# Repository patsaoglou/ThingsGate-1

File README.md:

#   ThingsGate-1

Gateway Motherboard powered by the ThingsCore-1 SOM. Featuring a LTE Modem, a LoraWAN Concentrator, PoE, battery power and solar charging, it is capable of supporting off-grid IoT applications.

#   Realistic View (Comming Soon...)

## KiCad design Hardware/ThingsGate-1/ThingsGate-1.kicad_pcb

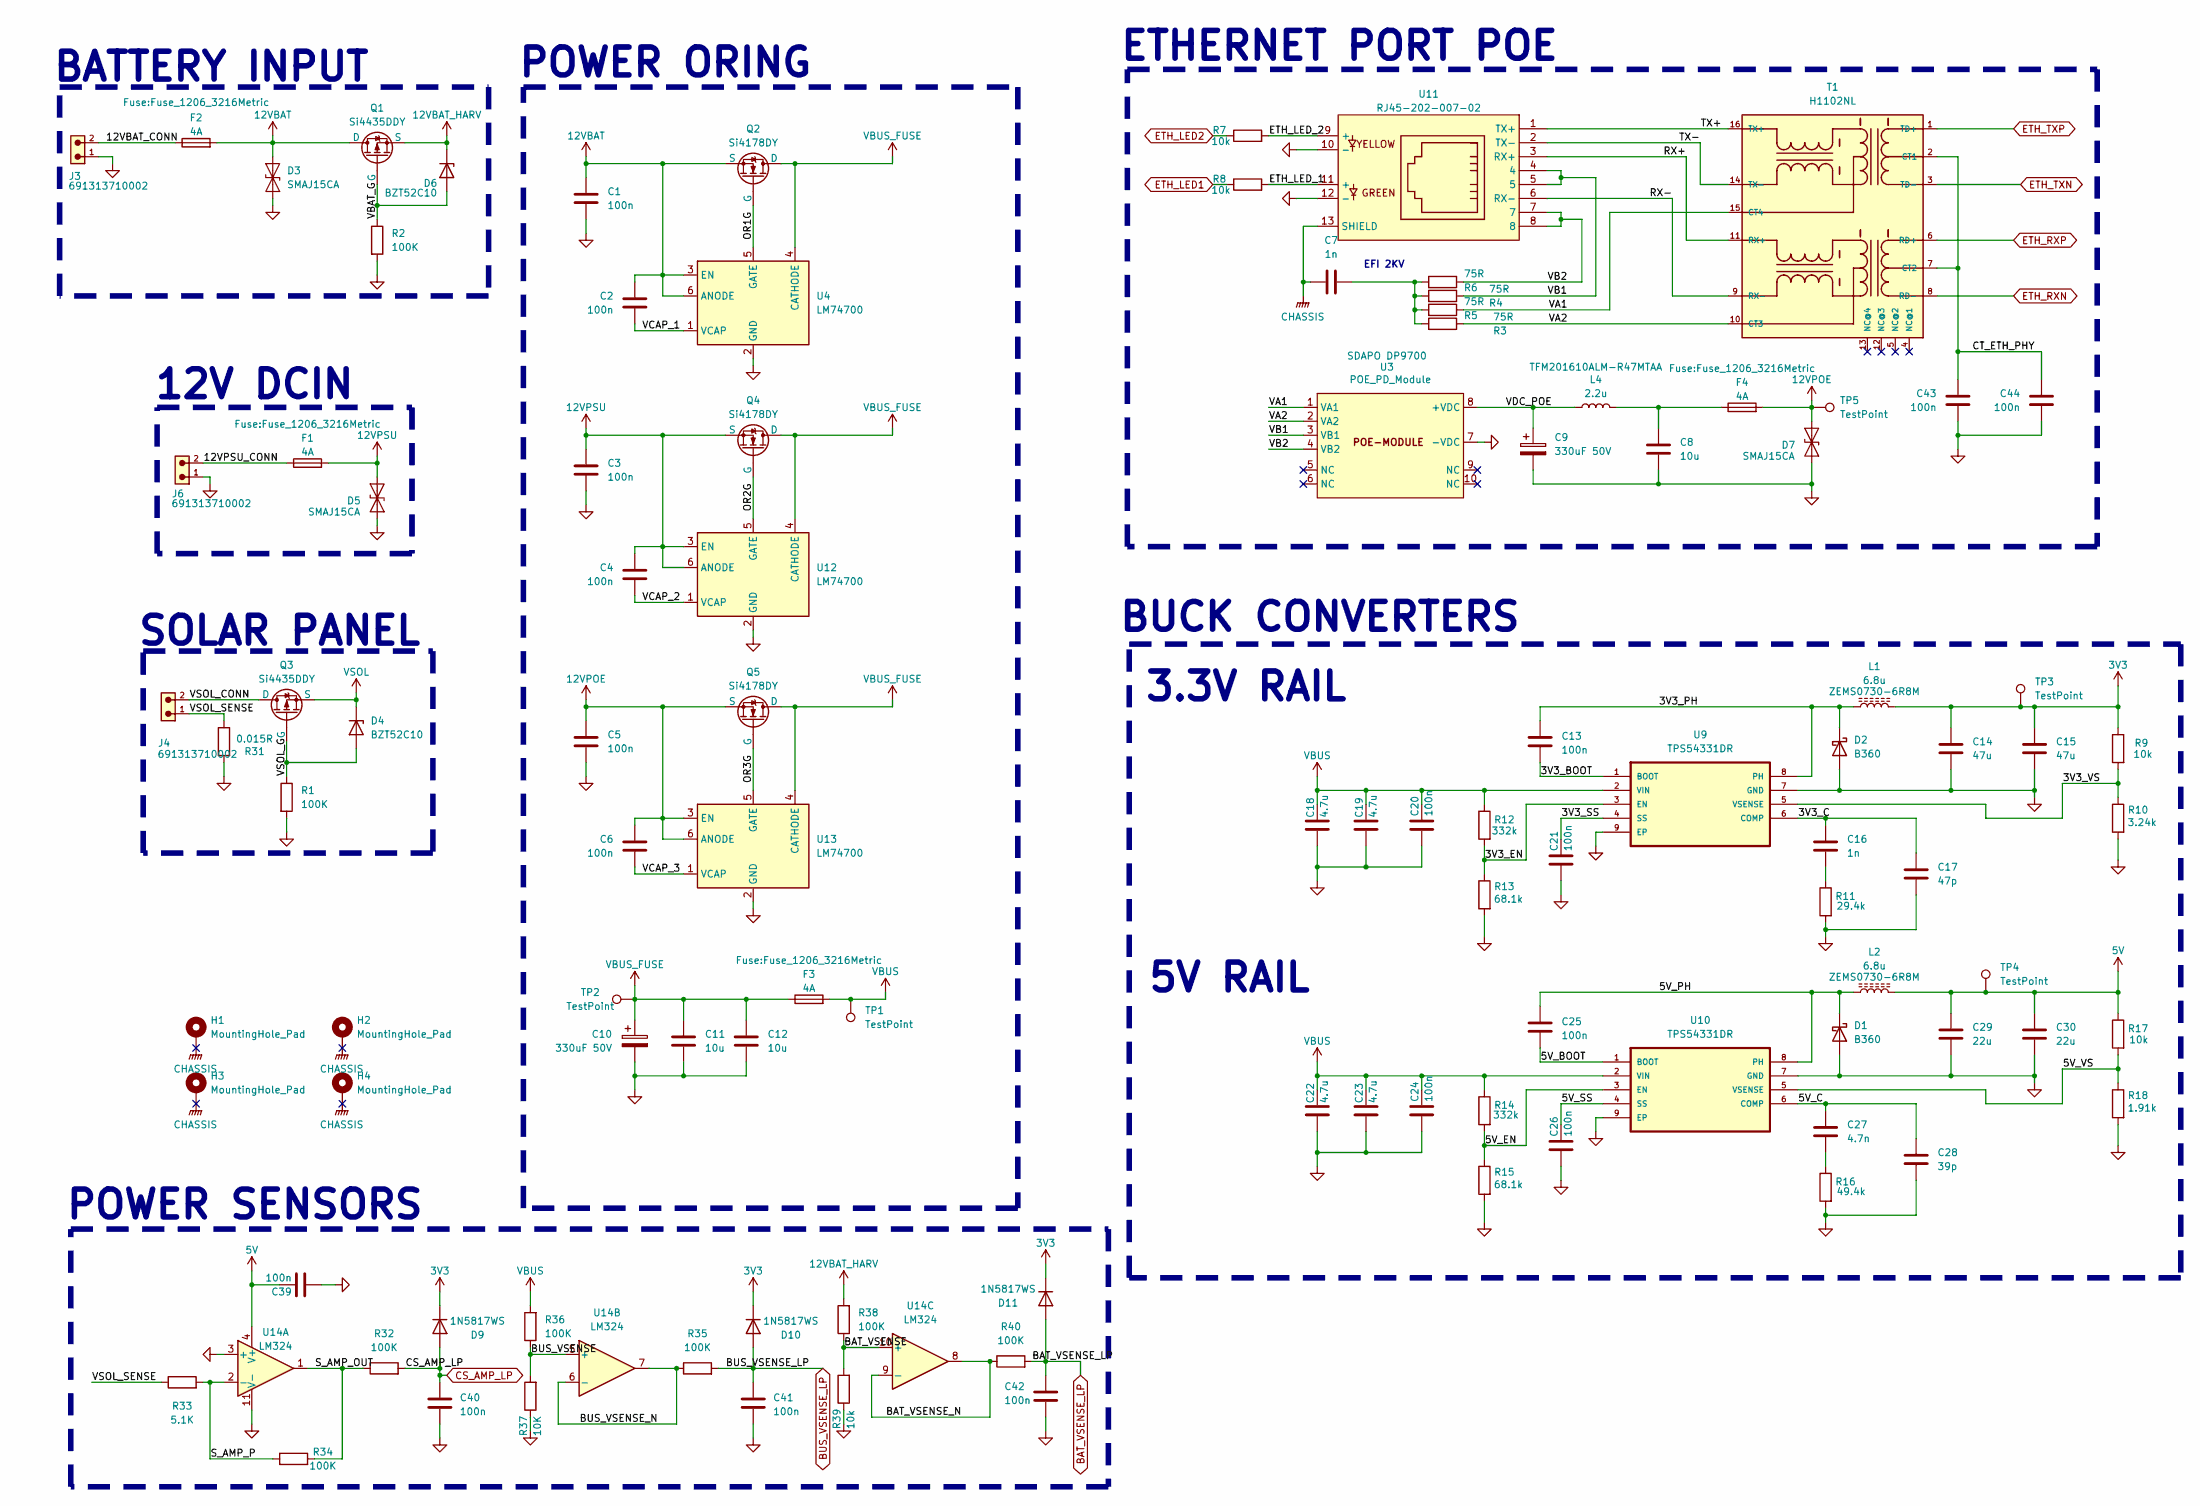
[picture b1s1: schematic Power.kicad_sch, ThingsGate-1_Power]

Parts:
C1, C2, C3, C4, C5, C6, C13, C20, C21, C24, C25, C26, C39, C40, C41, C42, C43, C44: 100n; C_0603_1608Metric
C7: 1n; C_1206_3216Metric
C8: 10u; Fuse_0805_2012Metric
C9, C10: 330uF 50V; CP_Elec_10x10.5
C11, C12: 10u; C_0805_2012Metric
C14, C15: 47u; C_0805_2012Metric
C16: 1n; C_0603_1608Metric
C17: 47p; C_0603_1608Metric
C18, C19, C22, C23: 4.7u; C_0805_2012Metric
C27: 4.7n; C_0603_1608Metric
C28: 39p; C_0603_1608Metric
C29, C30: 22u; C_0805_2012Metric
D1, D2: B360; D_SMA
D3, D5, D7: SMAJ15CA; D_SMA
D4, D6: BZT52C10; D_SOD-123
D9, D10, D11: 1N5817WS; D_SOD-323
F1, F2, F3, F4: 4A; Fuse_1206_3216Metric
H1, H2, H3, H4: MountingHole_Pad; MountingHole_3.2mm_M3_DIN965_Pad_TopBottom
J3, J4, J6: 691313710002
L1, L2: 6.8u; L_0730-6R8M
L4: 2.2u; L_0805_2016
Q1, Q3: Si4435DDY; SO-8_3.9x4.9mm_P1.27mm
Q2, Q4, Q5: Si4178DY; SO-8_3.9x4.9mm_P1.27mm
R1, R2, R32, R34, R35, R36, R38, R40: 100K; R_0603_1608Metric
R3, R4, R5, R6: 75R; R_0603_1608Metric
R7, R8, R9, R17, R39: 10k; R_0603_1608Metric
R10: 3.24k; R_0603_1608Metric
R11: 29.4k; R_0603_1608Metric
R12, R14: 332k; R_0603_1608Metric
R13, R15: 68.1k; R_0603_1608Metric
R16: 49.4k; R_0603_1608Metric
R18: 1.91k; R_0603_1608Metric
R31: 0.015R; R_1206_3216Metric
R33: 5.1K; R_0603_1608Metric
R37: 10K; R_0603_1608Metric
T1: H1102NL
TP1, TP2, TP3, TP4, TP5: TestPoint; TestPoint_Pad_D1.5mm
U3: POE_PD_Module; SDAPO_DP9700; Part SDAPO DP9700
U4, U12, U13: LM74700; SOT-23-6
U9, U10: TPS54331DR; TPS54331DDAR_PowerPAD
U11: RJ45-202-007-02; RJ45-TH_RJ45-202-007-02
U14: LM324; SOIC-14_3.9x8.7mm_P1.27mm

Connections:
3V3: C14.1, C15.1, D9.1 (K), D10.1 (K), D11.1 (K), L1.2, R9.1, TP3.1; also elsewhere on the board
5V: C29.1, C30.1, C39.1, L2.2, R17.1, TP4.1, U14.4 (V+); also elsewhere on the board
12VBAT: C1.1, C2.1, D3.2 (A2), F2.2, Q1.5 (D), Q1.6 (D), Q1.7 (D), Q1.8 (D), Q2.1 (S), Q2.2 (S), Q2.3 (S), U4.3 (EN), U4.6 (ANODE)
12VBAT_HARV: D6.1 (K), Q1.1 (S), Q1.2 (S), Q1.3 (S), R38.2; also elsewhere on the board
12VPOE: C5.1, C6.1, D7.2 (A2), F4.2, Q5.1 (S), Q5.2 (S), Q5.3 (S), TP5.1, U13.3 (EN), U13.6 (ANODE)
12VPSU: C3.1, C4.1, D5.2 (A2), F1.2, Q4.1 (S), Q4.2 (S), Q4.3 (S), U12.3 (EN), U12.6 (ANODE)
/Power Supply/3V3_BOOT: C13.2, U9.1 (BOOT)
/Power Supply/3V3_C: C16.1, C17.1, U9.6 (COMP)
/Power Supply/3V3_EN: R12.2, R13.1, U9.3 (EN)
/Power Supply/3V3_PH: C13.1, D2.1 (K), L1.1, U9.8 (PH)
/Power Supply/3V3_SS: C21.1, U9.4 (SS)
/Power Supply/3V3_VS: R9.2, R10.1, U9.5 (VSENSE)
/Power Supply/5V_BOOT: C25.2, U10.1 (BOOT)
/Power Supply/5V_C: C27.1, C28.1, U10.6 (COMP)
/Power Supply/5V_EN: R14.2, R15.1, U10.3 (EN)
/Power Supply/5V_PH: C25.1, D1.1 (K), L2.1, U10.8 (PH)
/Power Supply/5V_SS: C26.1, U10.4 (SS)
/Power Supply/5V_VS: R17.2, R18.1, U10.5 (VSENSE)
/Power Supply/12VBAT_CONN: F2.1, J3.2
/Power Supply/12VPSU_CONN: F1.1, J6.2
/Power Supply/BAT_VSENSE: R38.1, R39.2, U14.10 (+)
/Power Supply/BAT_VSENSE_N: R40.1, U14.8, U14.9 (-)
/Power Supply/BUS_VSENSE: R36.1, R37.2, U14.5 (+)
/Power Supply/BUS_VSENSE_N: R35.1, U14.6 (-), U14.7
/Power Supply/CT_ETH_PHY: C43.1, C44.1, T1.2 (CT1), T1.7 (CT2)
/Power Supply/ETH_LED_1: R8.2, U11.11 (+)
/Power Supply/ETH_LED_2: R7.2, U11.9 (+)
/Power Supply/OR1G: Q2.4 (G), U4.5 (GATE)
/Power Supply/OR2G: Q4.4 (G), U12.5 (GATE)
/Power Supply/OR3G: Q5.4 (G), U13.5 (GATE)
/Power Supply/RX+: T1.11 (RX+), U11.3 (RX+)
/Power Supply/RX-: T1.9 (RX-), U11.6 (RX-)
/Power Supply/S_AMP_OUT: R32.1, R34.2, U14.1
/Power Supply/S_AMP_P: R33.2, R34.1, U14.2 (-)
/Power Supply/TX+: T1.16 (TX+), U11.1 (TX+)
/Power Supply/TX-: T1.14 (TX-), U11.2 (TX-)
/Power Supply/VA1: R5.1, T1.15 (CT4), U3.1 (VA1)
/Power Supply/VA2: R3.1, T1.10 (CT3), U3.2 (VA2)
/Power Supply/VB1: R4.1, U3.3 (VB1), U11.4, U11.5
/Power Supply/VB2: R6.1, U3.4 (VB2), U11.7, U11.8
/Power Supply/VBAT_G: D6.2 (A), Q1.4 (G), R2.1
/Power Supply/VCAP_1: C2.2, U4.1 (VCAP)
/Power Supply/VCAP_2: C4.2, U12.1 (VCAP)
/Power Supply/VCAP_3: C6.2, U13.1 (VCAP)
/Power Supply/VDC_POE: C9.1, L4.1, U3.8 (+VDC)
/Power Supply/VSOL_CONN: J4.2, Q3.5 (D), Q3.6 (D), Q3.7 (D), Q3.8 (D)
/Power Supply/VSOL_G: D4.2 (A), Q3.4 (G), R1.1
/Power Supply/VSOL_SENSE: J4.1, R31.1, R33.1
BAT_VSENSE_LP: C42.2, D11.2 (A), R40.2; also elsewhere on the board
BUS_VSENSE_LP: C41.2, D10.2 (A), R35.2; also elsewhere on the board
CHASSIS: C7.1, H1.1, H2.1, H3.1, H4.1, U11.13 (SHIELD); also elsewhere on the board
CS_AMP_LP: C40.2, D9.2 (A), R32.2; also elsewhere on the board
ETH_LED1: R8.1; also elsewhere on the board
ETH_LED2: R7.1; also elsewhere on the board
ETH_RXN: T1.8 (RD-); also elsewhere on the board
ETH_RXP: T1.6 (RD+); also elsewhere on the board
ETH_TXN: T1.3 (TD-); also elsewhere on the board
ETH_TXP: T1.1 (TD+); also elsewhere on the board
GND: C1.2, C3.2, C5.2, C8.2, C9.2, C10.2, C11.2, C12.2, C14.2, C15.2, C17.2, C18.2, C19.2, C20.2, C21.2, C22.2, C23.2, C24.2, C26.2, C28.2, C29.2, C30.2, C39.2, C40.1, C41.1, C42.1, C43.2, C44.2, D1.2 (A), D2.2 (A), D3.1 (A1), D5.1 (A1), D7.1 (A1), J3.1, J6.1, R1.2, R2.2, R10.2, R11.2, R13.2, R15.2, R16.2, R18.2, R31.2, R37.1, R39.1, U3.7 (-VDC), U4.2 (GND), U9.7 (GND), U9.9 (EP), U10.7 (GND), U10.9 (EP), U11.10 (-), U11.12 (-), U12.2 (GND), U13.2 (GND), U14.3 (+), U14.11 (V-); also elsewhere on the board
unnamed: C7.2, R3.2, R4.2, R5.2, R6.2
unnamed: C8.1, F4.1, L4.2
unnamed: C16.2, R11.1
unnamed: C27.2, R16.1
VBUS: C18.1, C19.1, C20.1, C22.1, C23.1, C24.1, F3.2, R12.1, R14.1, R36.2, TP1.1, U9.2 (VIN), U10.2 (VIN)
VBUS_FUSE: C10.1, C11.1, C12.1, F3.1, Q2.5 (D), Q2.6 (D), Q2.7 (D), Q2.8 (D), Q4.5 (D), Q4.6 (D), Q4.7 (D), Q4.8 (D), Q5.5 (D), Q5.6 (D), Q5.7 (D), Q5.8 (D), TP2.1, U4.4 (CATHODE), U12.4 (CATHODE), U13.4 (CATHODE)
VSOL: D4.1 (K), Q3.1 (S), Q3.2 (S), Q3.3 (S); also elsewhere on the board

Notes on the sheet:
BUCK CONVERTERS
ETHERNET PORT POE
BATTERY INPUT
3.3V RAIL
POWER SENSORS
5V RAIL
SOLAR PANEL
EFI 2KV
12V DCIN
POWER ORING

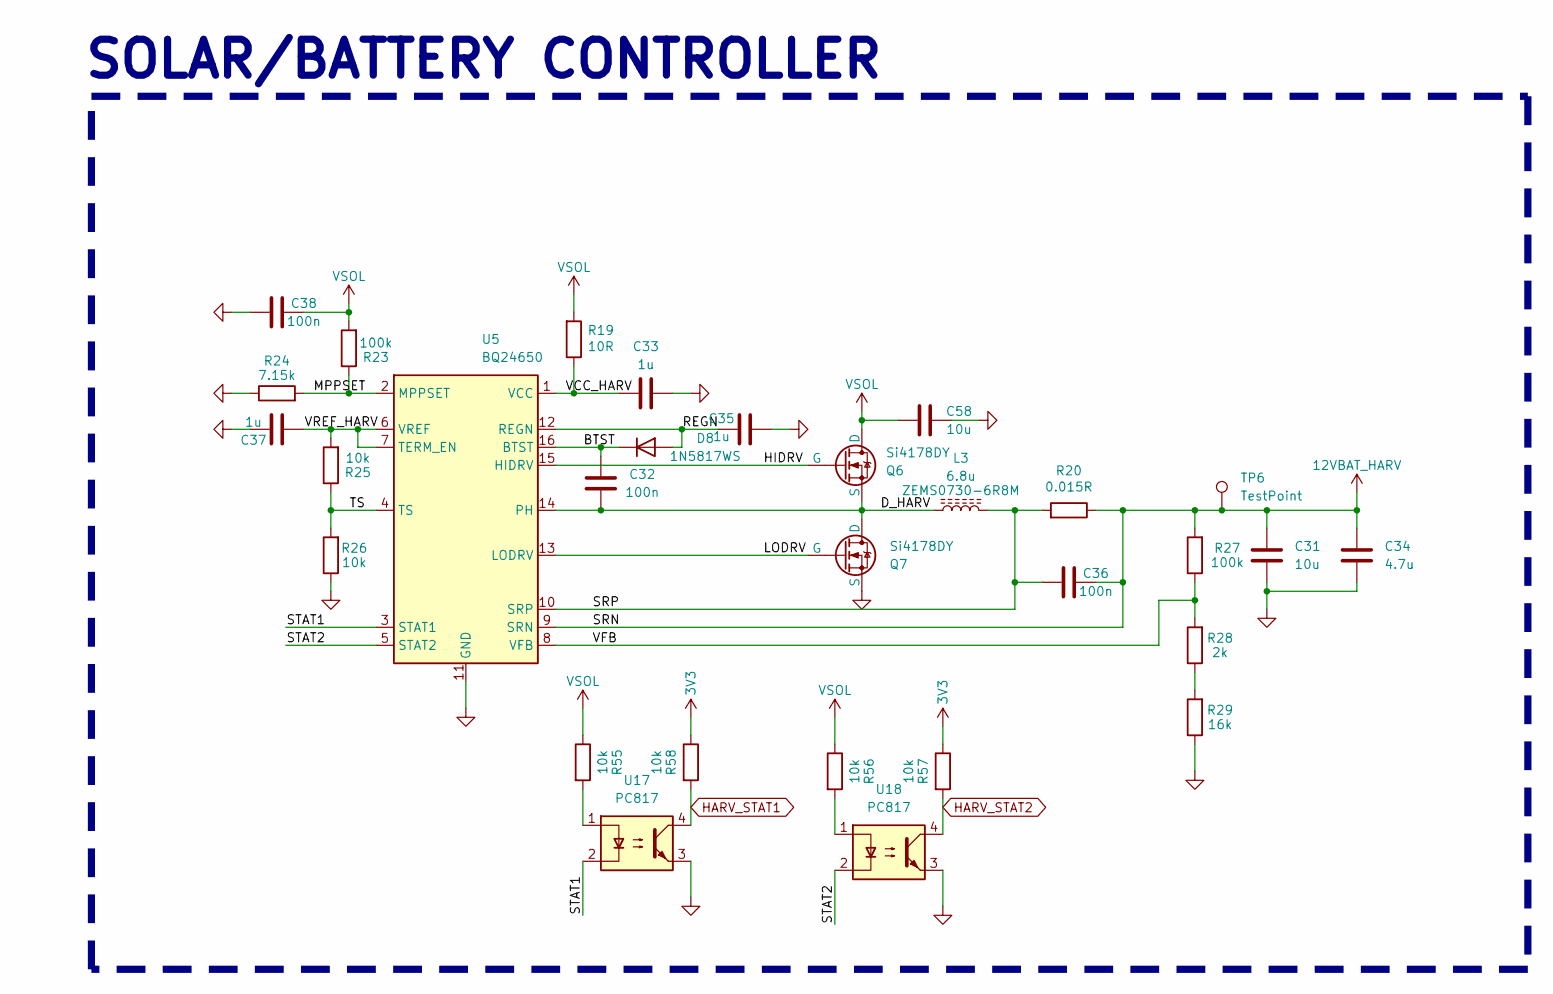
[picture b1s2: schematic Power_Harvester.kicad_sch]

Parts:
C31, C58: 10u; Fuse_0805_2012Metric
C32, C36, C38: 100n; C_0603_1608Metric
C33, C35, C37: 1u; Fuse_0805_2012Metric
C34: 4.7u; Fuse_0805_2012Metric
D8: 1N5817WS; D_SOD-323
L3: 6.8u; L_0730-6R8M
Q6, Q7: Si4178DY; SO-8_3.9x4.9mm_P1.27mm
R19: 10R; R_1206_3216Metric
R20: 0.015R; R_1206_3216Metric
R23, R27: 100k; R_0603_1608Metric
R24: 7.15k; R_0603_1608Metric
R25, R26, R55, R56, R57, R58: 10k; R_0603_1608Metric
R28: 2k; R_0603_1608Metric
R29: 16k; R_0603_1608Metric
TP6: TestPoint; TestPoint_Pad_D1.5mm
U5: BQ24650; Texas_RVA_VQFN-16-1EP_3.5x3.5mm_P0.5mm_EP2.14x2.14mm_Therma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
U17, U18: PC817; DIP-4_W7.62mm_SMDSocket_SmallPads

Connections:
3V3: R57.1, R58.1; also elsewhere on the board
12VBAT_HARV: C31.1, C34.1, C36.2, R20.1, R27.2, TP6.1, U5.9 (SRN); also elsewhere on the board
/Power Harvester/BTST: C32.1, D8.1 (K), U5.16 (BTST)
/Power Harvester/D_HARV: C32.2, L3.1, Q6.1 (S), Q6.2 (S), Q6.3 (S), Q7.5 (D), Q7.6 (D), Q7.7 (D), Q7.8 (D), U5.14 (PH)
/Power Harvester/HIDRV: Q6.4 (G), U5.15 (HIDRV)
/Power Harvester/LODRV: Q7.4 (G), U5.13 (LODRV)
/Power Harvester/MPPSET: R23.1, R24.2, U5.2 (MPPSET)
/Power Harvester/REGN: C35.2, D8.2 (A), U5.12 (REGN)
/Power Harvester/SRP: C36.1, L3.2, R20.2, U5.10 (SRP)
/Power Harvester/STAT1: U5.3 (STAT1), U17.2
/Power Harvester/STAT2: U5.5 (STAT2), U18.2
/Power Harvester/TS: R25.1, R26.2, U5.4 (TS)
/Power Harvester/VCC_HARV: C33.1, R19.1, U5.1 (VCC)
/Power Harvester/VFB: R27.1, R28.2, U5.8 (VFB)
/Power Harvester/VREF_HARV: C37.1, R25.2, U5.6 (VREF), U5.7 (TERM_EN)
GND: C31.2, C33.2, C34.2, C35.1, C37.2, C38.1, C58.2, Q7.1 (S), Q7.2 (S), Q7.3 (S), R24.1, R26.1, R29.1, U5.11 (GND), U5.17 (GND), U17.3, U18.3; also elsewhere on the board
HARV_STAT1: R58.2, U17.4; also elsewhere on the board
HARV_STAT2: R57.2, U18.4; also elsewhere on the board
unnamed: R28.1, R29.2
unnamed: R55.2, U17.1
unnamed: R56.2, U18.1
VSOL: C38.2, C58.1, Q6.5 (D), Q6.6 (D), Q6.7 (D), Q6.8 (D), R19.2, R23.2, R55.1, R56.1; also elsewhere on the board

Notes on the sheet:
SOLAR/BATTERY CONTROLLER

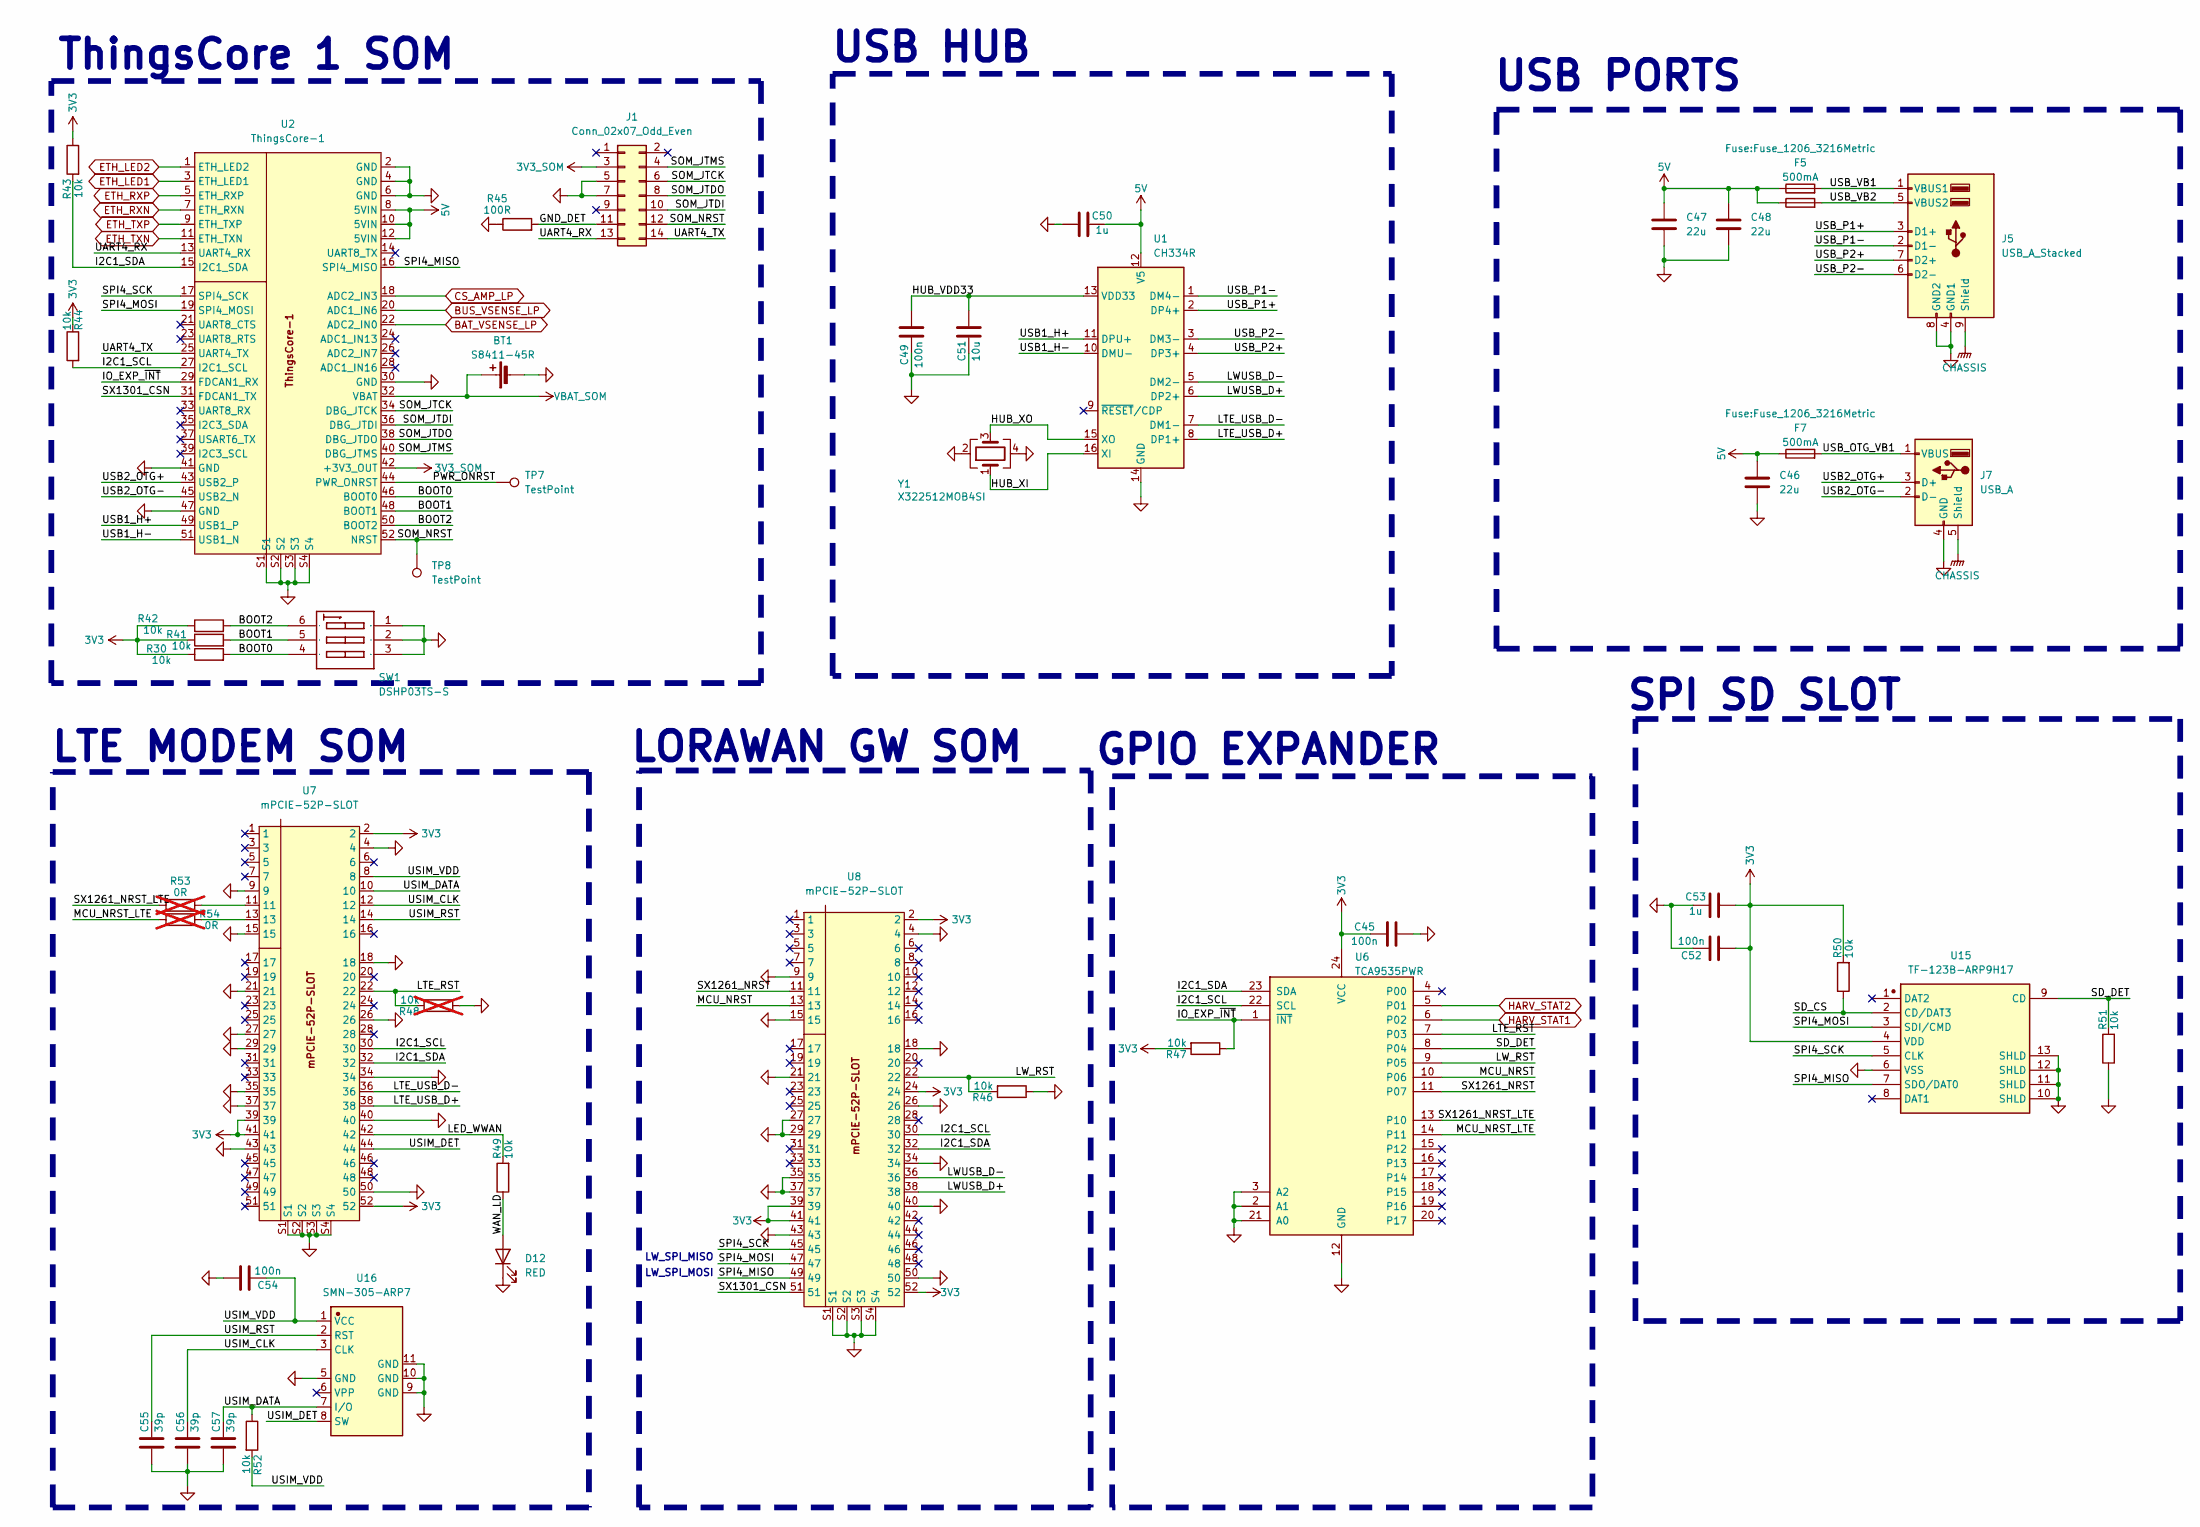
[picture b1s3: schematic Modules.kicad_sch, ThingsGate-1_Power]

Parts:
BT1: S8411-45R; Battery_Holder_CR1220_S8411-45R
C45, C49, C52, C54: 100n; C_0603_1608Metric
C46, C47, C48: 22u; C_0805_2012Metric
C50, C53: 1u; Fuse_0805_2012Metric
C51: 10u; Fuse_0805_2012Metric
C55, C56, C57: 39p; C_0603_1608Metric
D12: RED; LED_0603_1608Metric
F5, F6, F7: 500mA; Fuse_1206_3216Metric
J1: Conn_02x07_Odd_Even; IDC-Header_2x07_P2.54mm_Vertical
J5: USB_A_Stacked; DUAL_USB-TYPE_A
J7: USB_A; USB-A-TH_AF-ZJB13.7
R30, R41, R42, R43, R44, R46, R47, R49, R50, R51, R52: 10k; R_0603_1608Metric
R45: 100R; R_0603_1608Metric
R48: 10k; R_0603_1608Metric; not fitted
R53, R54: 0R; R_0603_1608Metric; not fitted
SW1: DSHP03TS-S; SW-SMD_DSHP03TS-S
TP7, TP8: TestPoint; TestPoint_Pad_D1.5mm
U1: CH334R; QSOP-16_3.9x4.9mm_P0.635mm
U2: ThingsCore-1
U6: TCA9535PWR; SSOP-24_5.3x8.2mm_P0.65mm
U7, U8: mPCIE-52P-SLOT; mpcie-slot_full
U15: TF-123B-ARP9H17; TF-SMD_TF-123-ARP9H15
U16: SMN-305-ARP7; NANO-SIM-SMD_SMN-305-ARP7
Y1: X322512MOB4SI; Crystal_SMD_3225-4Pin_3.2x2.5mm

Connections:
3V3: C45.1, C52.1, C53.1, R30.1, R41.1, R42.1, R43.1, R44.1, R47.2, R50.2, U6.24 (VCC), U7.2, U7.39, U7.41, U7.52, U8.2, U8.24, U8.39, U8.41, U8.52, U15.4 (VDD); also elsewhere on the board
3V3_SOM: J1.3, U2.42 (+3V3_OUT)
5V: C46.1, C47.1, C48.1, C50.2, F5.1, F6.1, F7.1, U1.12 (V5), U2.8 (5VIN), U2.10 (5VIN), U2.12 (5VIN); also elsewhere on the board
/Modules/BOOT0: R30.2, SW1.4, U2.46 (BOOT0)
/Modules/BOOT1: R41.2, SW1.5, U2.48 (BOOT1)
/Modules/BOOT2: R42.2, SW1.6, U2.50 (BOOT2)
/Modules/GND_DET: J1.11, R45.2
/Modules/HUB_VDD33: C49.1, C51.1, U1.13 (VDD33)
/Modules/HUB_XI: U1.16 (XI), Y1.1
/Modules/HUB_XO: U1.15 (XO), Y1.3
/Modules/I2C1_SCL: R44.2, U2.27 (I2C1_SCL), U6.22 (SCL), U7.30, U8.30
/Modules/I2C1_SDA: R43.2, U2.15 (I2C1_SDA), U6.23 (SDA), U7.32, U8.32
/Modules/IO_EXP_~INT: R47.1, U2.29 (FDCAN1_RX), U6.1 (~INT)
/Modules/LED_WWAN: R49.2, U7.42
/Modules/LTE_RST: R48.2, U6.7 (P03), U7.22
/Modules/LTE_USB_D+: U1.8 (DP1+), U7.38
/Modules/LTE_USB_D-: U1.7 (DM1-), U7.36
/Modules/LWUSB_D+: U1.6 (DP2+), U8.38
/Modules/LWUSB_D-: U1.5 (DM2-), U8.36
/Modules/LW_RST: R46.2, U6.9 (P05), U8.22
/Modules/MCU_NRST: U6.10 (P06), U8.13
/Modules/MCU_NRST_LTE: R54.1, U6.14 (P11)
/Modules/PWR_ONRST: TP7.1, U2.44 (PWR_ONRST)
/Modules/SD_CS: R50.1, U15.2 (CD/DAT3)
/Modules/SD_DET: R51.2, U6.8 (P04), U15.9 (CD)
/Modules/SOM_JTCK: J1.6, U2.34 (DBG_JTCK)
/Modules/SOM_JTDI: J1.10, U2.36 (DBG_JTDI)
/Modules/SOM_JTDO: J1.8, U2.38 (DBG_JTDO)
/Modules/SOM_JTMS: J1.4, U2.40 (DBG_JTMS)
/Modules/SOM_NRST: J1.12, TP8.1, U2.52 (NRST)
/Modules/SPI4_MISO: U2.16 (SPI4_MISO), U8.49, U15.7 (SDO/DAT0)
/Modules/SPI4_MOSI: U2.19 (SPI4_MOSI), U8.47, U15.3 (SDI/CMD)
/Modules/SPI4_SCK: U2.17 (SPI4_SCK), U8.45, U15.5 (CLK)
/Modules/SX1261_NRST: U6.11 (P07), U8.11
/Modules/SX1261_NRST_LTE: R53.2, U6.13 (P10)
/Modules/SX1301_CSN: U2.31 (FDCAN1_TX), U8.51
/Modules/UART4_RX: J1.13, U2.13 (UART4_RX)
/Modules/UART4_TX: J1.14, U2.25 (UART4_TX)
/Modules/USB1_H+: U1.11 (DPU+), U2.49 (USB1_P)
/Modules/USB1_H-: U1.10 (DMU-), U2.51 (USB1_N)
/Modules/USB2_OTG+: J7.3 (D+), U2.43 (USB2_P)
/Modules/USB2_OTG-: J7.2 (D-), U2.45 (USB2_N)
/Modules/USB_OTG_VB1: F7.2, J7.1 (VBUS)
/Modules/USB_P1+: J5.3 (D1+), U1.2 (DP4+)
/Modules/USB_P1-: J5.2 (D1-), U1.1 (DM4-)
/Modules/USB_P2+: J5.7 (D2+), U1.4 (DP3+)
/Modules/USB_P2-: J5.6 (D2-), U1.3 (DM3-)
/Modules/USB_VB1: F5.2, J5.1 (VBUS1)
/Modules/USB_VB2: F6.2, J5.5 (VBUS2)
/Modules/USIM_CLK: C56.1, U7.12, U16.3 (CLK)
/Modules/USIM_DATA: C57.1, R52.1, U7.10, U16.7 (I/O)
/Modules/USIM_DET: U7.44, U16.8 (SW)
/Modules/USIM_RST: C55.1, U7.14, U16.2 (RST)
/Modules/USIM_VDD: C54.2, R52.2, U7.8, U16.1 (VCC)
/Modules/WAN_LD: D12.2 (A), R49.1
BAT_VSENSE_LP: U2.22 (ADC2_IN0); also elsewhere on the board
BUS_VSENSE_LP: U2.20 (ADC1_IN6); also elsewhere on the board
CHASSIS: J5.9 (Shield), J7.5 (Shield); also elsewhere on the board
CS_AMP_LP: U2.18 (ADC2_IN3); also elsewhere on the board
ETH_LED1: U2.3 (ETH_LED1); also elsewhere on the board
ETH_LED2: U2.1 (ETH_LED2); also elsewhere on the board
ETH_RXN: U2.7 (ETH_RXN); also elsewhere on the board
ETH_RXP: U2.5 (ETH_RXP); also elsewhere on the board
ETH_TXN: U2.11 (ETH_TXN); also elsewhere on the board
ETH_TXP: U2.9 (ETH_TXP); also elsewhere on the board
GND: BT1.2 (-), C45.2, C46.2, C47.2, C48.2, C49.2, C50.1, C51.2, C52.2, C53.2, C54.1, C55.2, C56.2, C57.2, D12.1 (K), J1.5, J1.7, J5.4 (GND1), J5.8 (GND2), J7.4 (GND), R45.1, R46.1, R48.1, R51.1, SW1.1, SW1.2, SW1.3, U1.14 (GND), U2.2 (GND), U2.4 (GND), U2.6 (GND), U2.30 (GND), U2.41 (GND), U2.47 (GND), U2.S1, U2.S2, U2.S3, U2.S4, U6.2 (A1), U6.3 (A2), U6.12 (GND), U6.21 (A0), U7.4, U7.9, U7.15, U7.18, U7.21, U7.26, U7.27, U7.29, U7.34, U7.35, U7.37, U7.40, U7.43, U7.50, U7.S1, U7.S2, U7.S3, U7.S4, U8.4, U8.9, U8.15, U8.18, U8.21, U8.26, U8.27, U8.29, U8.34, U8.35, U8.37, U8.40, U8.43, U8.50, U8.S1, U8.S2, U8.S3, U8.S4, U15.6 (VSS), U15.10 (SHLD), U15.11 (SHLD), U15.12 (SHLD), U15.13 (SHLD), U16.5 (GND), U16.9 (GND), U16.10 (GND), U16.11 (GND), Y1.2, Y1.4; also elsewhere on the board
HARV_STAT1: U6.6 (P02); also elsewhere on the board
HARV_STAT2: U6.5 (P01); also elsewhere on the board
unnamed: R53.1, U7.11
unnamed: R54.2, U7.13
VBAT_SOM: BT1.1 (+), U2.32 (VBAT)

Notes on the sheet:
LW_SPI_MISO
GPIO EXPANDER
USB HUB
LTE MODEM SOM
LORAWAN GW SOM
USB PORTS
SPI SD SLOT
ThingsCore 1 SOM
LW_SPI_MOSI

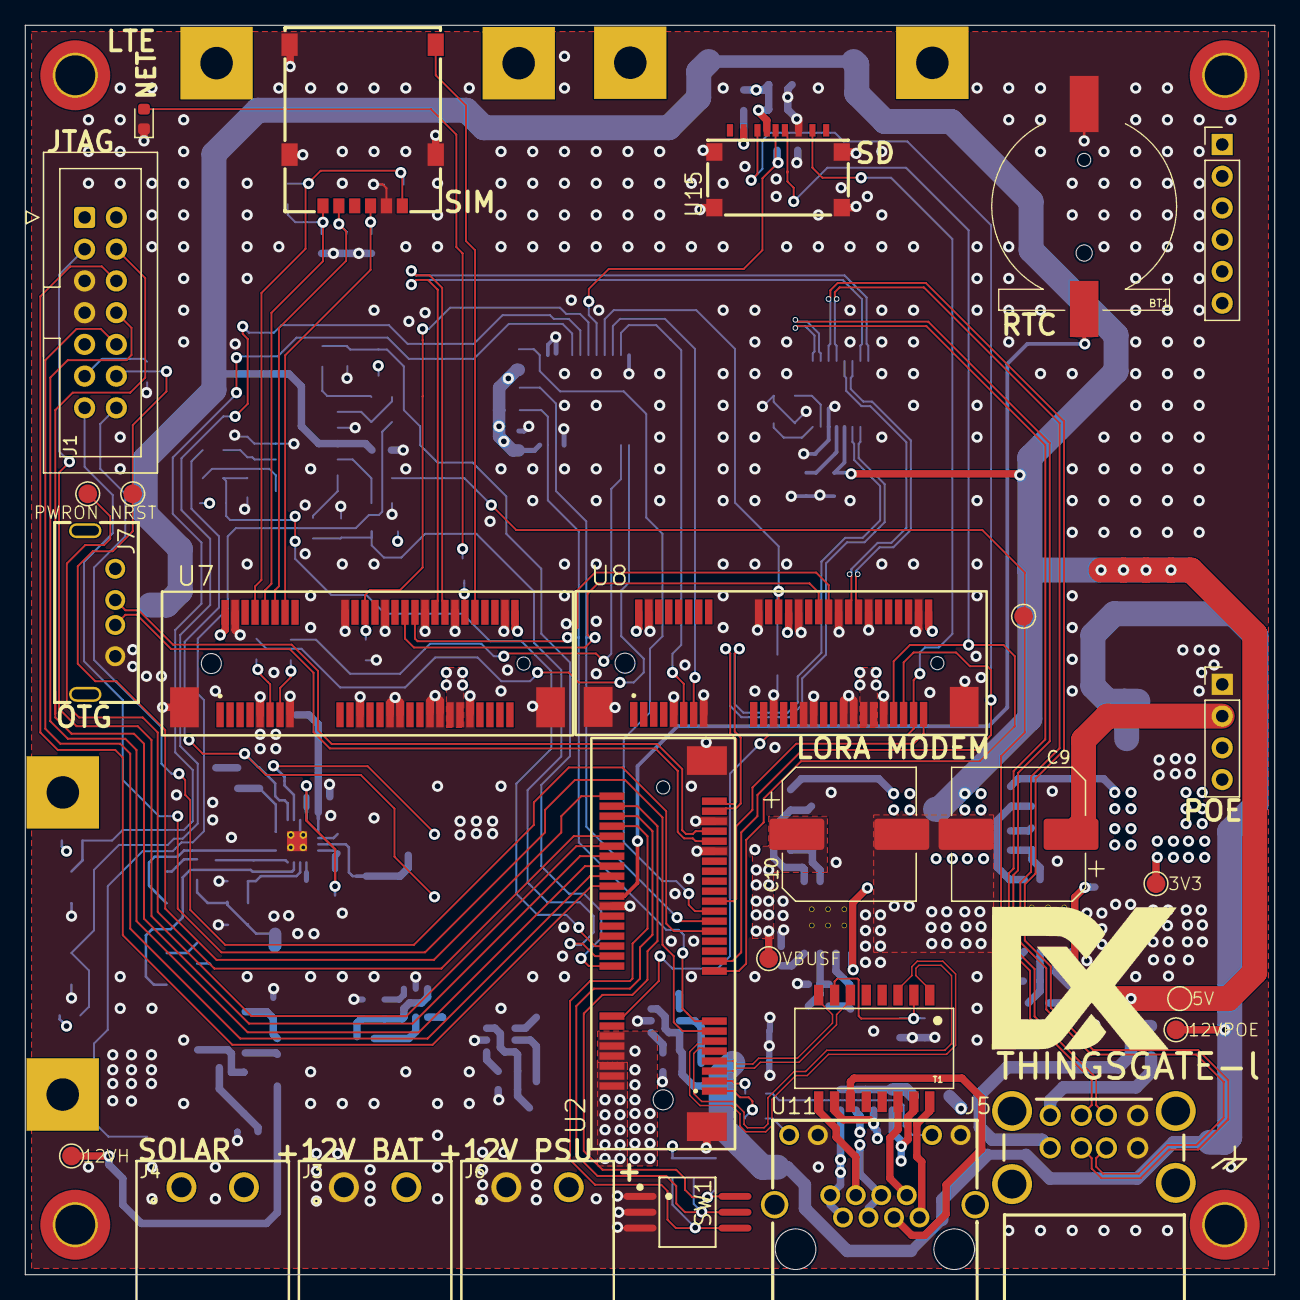
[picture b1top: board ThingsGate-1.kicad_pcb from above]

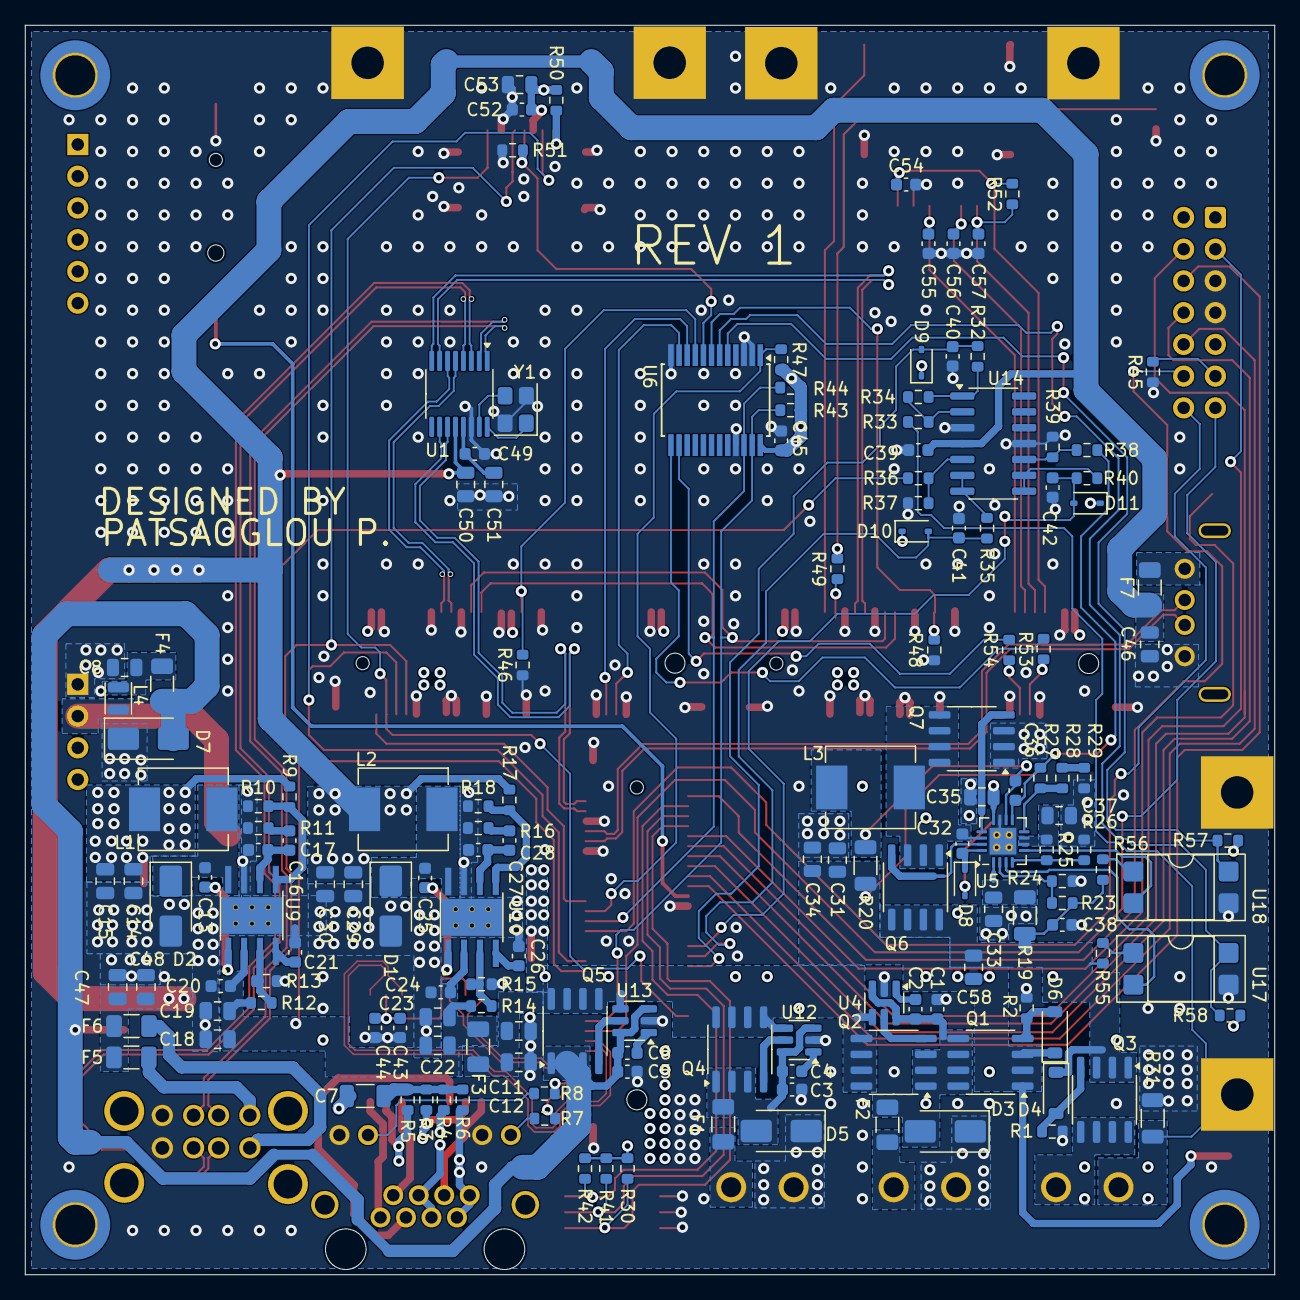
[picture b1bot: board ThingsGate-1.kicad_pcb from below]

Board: 4 copper layers, 100.0 x 100.0 mm, 184 parts (153 on the bottom side), 140 nets.

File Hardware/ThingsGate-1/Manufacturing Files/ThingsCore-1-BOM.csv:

"Reference","Qty","Value","DNP","Footprint"
"BT1","1","S8411-45R","","ThingsGate-1:Battery_Holder_CR1220_S8411-45R"
"C1,C2,C3,C4,C5,C6,C13,C20,C21,C24,C25,C26,C32,C36,C38,C39,C40,C41,C42,C43,C44,C45,C49,C52,C54","25","100n","","Capacitor_SMD:C_0603_1608Metric"
"C7","1","1n","","Capacitor_SMD:C_1206_3216Metric"
"C8,C31,C51,C58","4","10u","","Fuse:Fuse_0805_2012Metric"
"C9,C10","2","330uF 50V","","Capacitor_SMD:CP_Elec_10x10.5"
"C11,C12","2","10u","","Capacitor_SMD:C_0805_2012Metric"
"C14,C15","2","47u","","Capacitor_SMD:C_0805_2012Metric"
"C16","1","1n","","Capacitor_SMD:C_0603_1608Metric"
"C17","1","47p","","Capacitor_SMD:C_0603_1608Metric"
"C18,C19,C22,C23","4","4.7u","","Capacitor_SMD:C_0805_2012Metric"
"C27","1","4.7n","","Capacitor_SMD:C_0603_1608Metric"
"C28,C55,C56,C57","4","39p","","Capacitor_SMD:C_0603_1608Metric"
"C29,C30,C46,C47,C48","5","22u","","Capacitor_SMD:C_0805_2012Metric"
"C33,C35,C37,C50,C53","5","1u","","Fuse:Fuse_0805_2012Metric"
"C34","1","4.7u","","Fuse:Fuse_0805_2012Metric"
"D1,D2","2","B360","","Diode_SMD:D_SMA"
"D3,D5,D7","3","SMAJ15CA","","Diode_SMD:D_SMA"
"D4,D6","2","BZT52C10","","Diode_SMD:D_SOD-123"
"D8,D9,D10,D11","4","1N5817WS","","Diode_SMD:D_SOD-323"
"D12","1","RED","","LED_SMD:LED_0603_1608Metric"
"F1,F2,F3,F4","4","4A","","Fuse:Fuse_1206_3216Metric"
"F5,F6,F7","3","500mA","","Fuse:Fuse_1206_3216Metric"
"J1","1","Conn_02x07_Odd_Even","","Connector_IDC:IDC-Header_2x07_P2.54mm_Vertical"
"J3,J4,J6","3","691313710002","","ThingsGate-1:691313710002"
"J5","1","USB_A_Stacked","","ThingsGate-1:DUAL_USB-TYPE_A"
"J7","1","USB_A","","ThingsGate-1:USB-A-TH_AF-ZJB13.7"
"L1,L2,L3","3","6.8u","","ThingsGate-1:L_0730-6R8M"
"L4","1","2.2u","","ThingsGate-1:L_0805_2016"
"Q1,Q3","2","Si4435DDY","","ThingsGate-1:SO-8_3.9x4.9mm_P1.27mm"
"Q2,Q4,Q5,Q6,Q7","5","Si4178DY","","ThingsGate-1:SO-8_3.9x4.9mm_P1.27mm"
"R1,R2,R32,R34,R35,R36,R38,R40","8","100K","","Resistor_SMD:R_0603_1608Metric"
"R3,R4,R5,R6","4","75R","","Resistor_SMD:R_0603_1608Metric"
"R7,R8,R9,R17,R25,R26,R30,R39,R41,R42,R43,R44,R46,R47,R49,R50,R51,R52,R55,R56,R57,R58","22","10k","","Resistor_SMD:R_0603_1608Metric"
"R10","1","3.24k","","Resistor_SMD:R_0603_1608Metric"
"R11","1","29.4k","","Resistor_SMD:R_0603_1608Metric"
"R12,R14","2","332k","","Resistor_SMD:R_0603_1608Metric"
"R13,R15","2","68.1k","","Resistor_SMD:R_0603_1608Metric"
"R16","1","49.4k","","Resistor_SMD:R_0603_1608Metric"
"R18","1","1.91k","","Resistor_SMD:R_0603_1608Metric"
"R19","1","10R","","Resistor_SMD:R_1206_3216Metric"
"R20,R31","2","0.015R","","Resistor_SMD:R_1206_3216Metric"
"R23,R27","2","100k","","Resistor_SMD:R_0603_1608Metric"
"R24","1","7.15k","","Resistor_SMD:R_0603_1608Metric"
"R28","1","2k","","Resistor_SMD:R_0603_1608Metric"
"R29","1","16k","","Resistor_SMD:R_0603_1608Metric"
"R33","1","5.1K","","Resistor_SMD:R_0603_1608Metric"
"R37","1","10K","","Resistor_SMD:R_0603_1608Metric"
"R45","1","100R","","Resistor_SMD:R_0603_1608Metric"
"SW1","1","DSHP03TS-S","","ThingsGate-1:SW-SMD_DSHP03TS-S"
"T1","1","H1102NL","","ThingsGate-1:H1102NL"
"TP1,TP2,TP3,TP4,TP5,TP6,TP7,TP8","8","TestPoint","","TestPoint:TestPoint_Pad_D1.5mm"
"U1","1","CH334R","","Package_SO:QSOP-16_3.9x4.9mm_P0.635mm"
"U2","1","ThingsCore-1","","ThingsGate-1:ThingsCore-1"
"U3","1","POE_PD_Module","","ThingsGate-1:SDAPO_DP9700"
"U4,U12,U13","3","LM74700","","Package_TO_SOT_SMD:SOT-23-6"
"U5","1","BQ24650","","ThingsGate-1:Texas_RVA_VQFN-16-1EP_3.5x3.5mm_P0.5mm_EP2.14x2.14mm_ThermalVias"
"U6","1","TCA9535PWR","","Package_SO:SSOP-24_5.3x8.2mm_P0.65mm"
"U7,U8","2","mPCIE-52P-SLOT","","ThingsGate-1:mpcie-slot_full"
"U9,U10","2","TPS54331DR","","ThingsGate-1:TPS54331DDAR_PowerPAD"
"U11","1","RJ45-202-007-02","","ThingsGate-1:RJ45-TH_RJ45-202-007-02"
"U14","1","LM324","","Package_SO:SOIC-14_3.9x8.7mm_P1.27mm"
"U15","1","TF-123B-ARP9H17","","ThingsGate-1:TF-SMD_TF-123-ARP9H15"
"U16","1","SMN-305-ARP7","","ThingsGate-1:NANO-SIM-SMD_SMN-305-ARP7"
"U17,U18","2","PC817","","Package_DIP:DIP-4_W7.62mm_SMDSocket_SmallPads"
"Y1","1","X322512MOB4SI","","Crystal:Crystal_SMD_3225-4Pin_3.2x2.5mm"

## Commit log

2025-09-20 init
2025-10-13 schematic
2025-10-14 harvester schematic ready
2025-10-20 mpcie wire-up
2025-10-21 placement ok
2025-10-22 layout finished. checks and fab files remaining
2025-10-22 final fab files and checks done
